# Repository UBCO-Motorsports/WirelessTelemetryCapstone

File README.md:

# WirelessTelemetryCapstone

Please see the UBCO Motorsports wiki page for a full description:
https://sites.google.com/view/ubcomotorsportswiki/electronics/wireless-telemetry-capstone

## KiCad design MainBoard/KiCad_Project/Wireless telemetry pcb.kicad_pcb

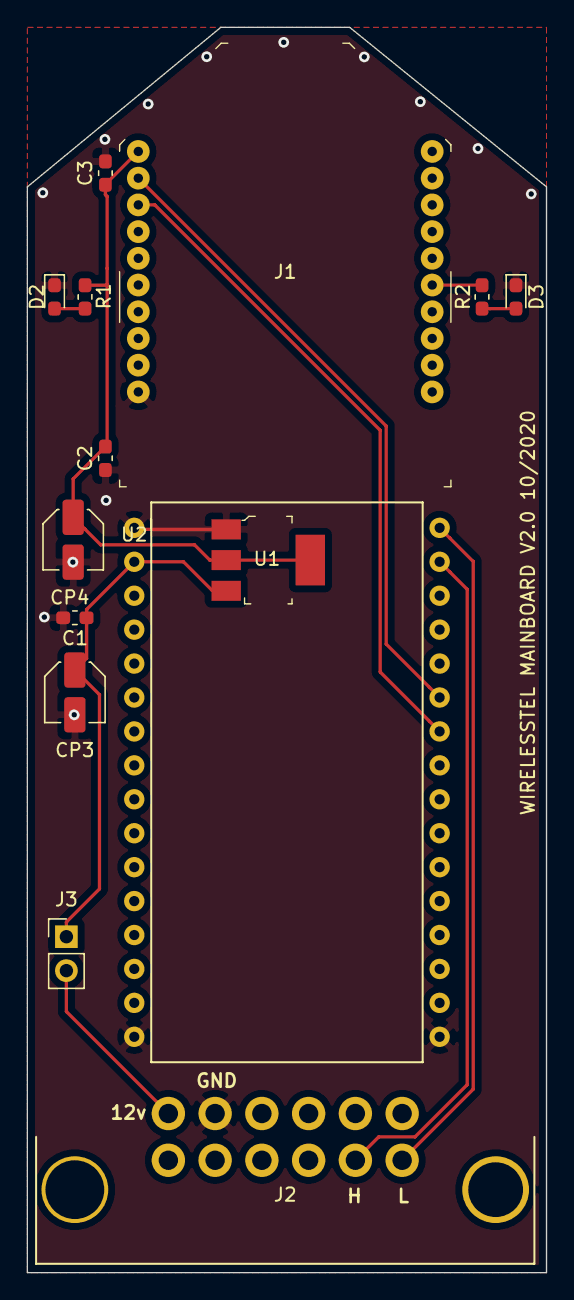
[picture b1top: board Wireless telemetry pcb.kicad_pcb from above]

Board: 2 copper layers, 38.9 x 93.2 mm, 14 parts (0 on the bottom side), 11 nets.

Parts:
C1, C2: 10nF; C_0603_1608Metric_Pad1.05x0.95mm_HandSolder
C3: 8.2pF; C_0603_1608Metric_Pad1.05x0.95mm_HandSolder
CP3, CP4: 10uF; C_Elec_4x5.4
D2, D3: LED; LED_0603_1608Metric_Pad1.05x0.95mm_HandSolder
J1: XBEE; XBEE_PRO-20_THT
J2: Molex MX120; MX120G
J3: PWR HDR; PinHeader_1x02_P2.54mm_Vertical
R1, R2: 220; R_0603_1608Metric_Pad1.05x0.95mm_HandSolder
U1: NCV1117ST33; SOT-223
U2: ControllerBoardV2; ControlBoardV2.0

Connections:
+12V: C1.1, CP3.1, J3.1, U1.3, U2.2
ASSOC: J1.15, R2.2
CANH: J2.11, U2.18
CANL: J2.12, U2.17
GND: C1.2, C2.2, C3.2, CP3.2, CP4.2, D2.1, D3.1, J1.10, J2.2, U1.1, U2.1, U2.16, U2.32
IN: J1.3, U2.23
unnamed: D2.2, R1.1
unnamed: D3.2, R2.1
unnamed: J2.1, J3.2
OUT: J1.2, U2.22
Vcc3.3V: C2.1, C3.1, CP4.1, J1.1, R1.2, U1.2

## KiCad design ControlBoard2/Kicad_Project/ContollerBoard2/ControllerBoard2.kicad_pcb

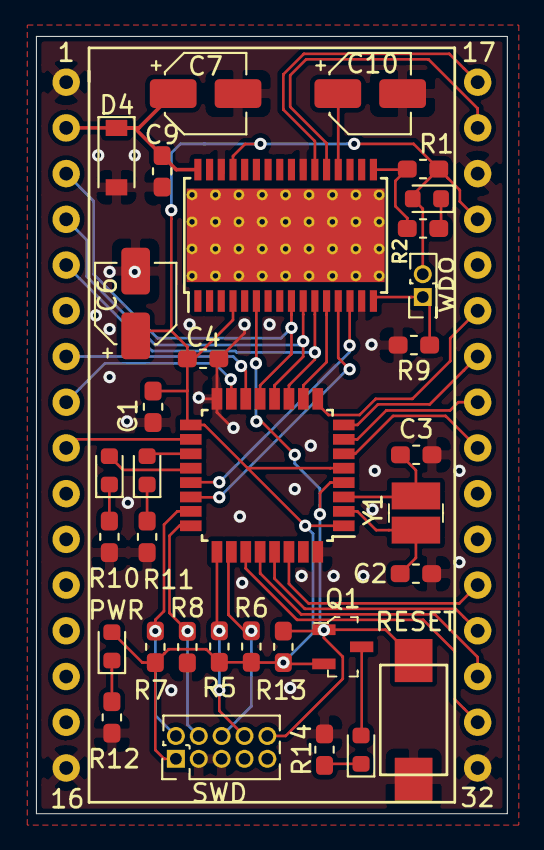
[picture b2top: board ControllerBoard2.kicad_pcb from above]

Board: 2 copper layers, 26.2 x 43.2 mm, 34 parts (0 on the bottom side), 40 nets.

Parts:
C1, C4, C9: 100n; C_0603_1608Metric_Pad1.05x0.95mm_HandSolder
C2, C3: 8p; C_0603_1608Metric_Pad1.05x0.95mm_HandSolder
C6, C7, C10: 10u; CP_Elec_4x5.4
D1, D6: LEDR; LED_0603_1608Metric
D2, D3, D5: LEDG; LED_0603_1608Metric
D4: 30v; D_SOD-123
J1: Main Header; Breadboard_Center_32pin
J2: SWD; PinHeader_2x05_P1.27mm_Vertical
J3: WD_Disable; PinHeader_2x01_P1.27mm_Vertical
Q1: BSS84; SOT-23-3
R1, R5, R6, R7, R8, R13: 10k; R_0603_1608Metric_Pad1.05x0.95mm_HandSolder
R2, R10, R11, R12, R14: 220; R_0603_1608Metric_Pad1.05x0.95mm_HandSolder
R9: 1.3k; R_0603_1608Metric_Pad1.05x0.95mm_HandSolder
S1: RESET; PTS636 SK25F SMTR LFS
U1: STM32F303K8Tx; LQFP-32_7x7mm_P0.8mm
U2: UJA1075A-3.3; HTSSOP-32-1EP_6.1x11mm_P0.65mm_EP5.2x11mm_Mask4.11x4.36mm_T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
Y1: 8Mhz; SMD-2_3.2x2.5mm

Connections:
+3V3: C1.2, C4.1, C6.1, D1.2, D5.2, J1.20, J2.1, J3.2, Q1.2, R1.1, R5.1, R6.1, R7.1, R13.1, U1.1, U1.5, U1.17, U2.4, U2.29
+12V: C7.1, C9.2, D4.1, J1.2, U2.32
CANH: J1.18, U2.21
CANL: J1.17, U2.22
CAN_RX: U1.21, U2.14
CAN_TX: U1.22, U2.13
GND: C1.1, C2.2, C3.2, C4.2, C6.2, C7.2, C9.1, C10.2, D4.2, J1.1, J1.16, J1.19, J1.32, J2.3, J2.5, R8.2, R9.2, R10.1, R11.1, R12.1, R14.2, S1.2, U1.16, U1.32, U2.15, U2.23, U2.30
LIMP: R1.2, R2.2, U2.17
MISO: J1.4, U1.12, U2.10
MOSI: J1.3, U1.13, U2.9
unnamed: C10.1, U2.20
unnamed: D1.1, R2.1
unnamed: D2.1, R10.2
unnamed: D3.1, R11.2
unnamed: D5.1, R12.2
unnamed: D6.1, R14.1
unnamed: D6.2, Q1.3
OSC_IN: C2.1, U1.2, Y1.1
OSC_OUT: C3.1, U1.3, Y1.2
PA0: J1.25, U1.6
PA1: J1.24, U1.7
PA2: J1.23, U1.8
PA3: J1.22, U1.9
PA8: J1.9, U1.18
PA9: D3.2, U1.19
PA10: D2.2, U1.20
PB0: J1.7, U1.14
PB1: J1.8, U1.15
PB4: J1.31, U1.27
PB5: J1.30, U1.28
PB6: J1.29, U1.29
PB7: J1.28, U1.30
RESET: J2.10, Q1.1, R13.2, S1.1, U1.4, U2.6
SCK: J1.5, U1.11, U2.11
SCSN: U1.10, U2.12
SWDCLK: J2.4, R8.1, U1.24
SWDIO: J2.2, R7.2, U1.23
SWO: J2.6, R6.2, U1.26
TDI: J2.8, R5.2, U1.25
WD_OFF: J3.1, R9.1, U2.16

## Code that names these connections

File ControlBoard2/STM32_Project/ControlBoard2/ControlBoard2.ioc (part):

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Mcu.Name=STM32F303K(6-8)Tx
Mcu.Package=LQFP32
Mcu.UserName=STM32F303K8Tx
PA10.GPIOParameters=GPIO_Label
PA10.GPIO_Label=LD1
PA10.Signal=GPIO_Output
PA11.Mode=CAN_Activate
PA11.Signal=CAN_RX
PA12.Mode=CAN_Activate
PA12.Signal=CAN_TX
PA13.Mode=JTAG_4_pins
PA13.Signal=SYS_JTMS-SWDIO
PA14.Mode=JTAG_4_pins
PA14.Signal=SYS_JTCK-SWCLK
PA15.Mode=JTAG_4_pins
PA15.Signal=SYS_JTDI
PA2.Mode=Asynchronous
PA2.Signal=USART2_TX
PA3.Mode=Asynchronous
PA3.Signal=USART2_RX
PA4.GPIOParameters=GPIO_Label
PA4.GPIO_Label=UJA_CS
PA4.Signal=GPIO_Output
PA5.Mode=Full_Duplex_Master
PA5.Signal=SPI1_SCK
PA6.Mode=Full_Duplex_Master
PA6.Signal=SPI1_MISO
PA7.Mode=Full_Duplex_Master
PA7.Signal=SPI1_MOSI
PA9.GPIOParameters=GPIO_Label
PA9.GPIO_Label=LD2
PA9.Signal=GPIO_Output
PB3.Mode=JTAG_4_pins
PB3.Signal=SYS_JTDO-TRACESWO
PB6.Mode=Asynchronous
PB6.Signal=USART1_TX
PB7.Mode=Asynchronous
PB7.Signal=USART1_RX
PF0\ /\ OSC_IN.Mode=HSE-External-Oscillator
PF0\ /\ OSC_IN.Signal=RCC_OSC_IN
PF1\ /\ OSC_OUT.Mode=HSE-External-Oscillator
PF1\ /\ OSC_OUT.Signal=RCC_OSC_OUT
RCC.HSEPLLFreq_Value=8000000
RCC.HSE_VALUE=8000000
RCC.SYSCLKFreq_VALUE=64000000
RCC.SYSCLKSourceVirtual=RCC_SYSCLKSOURCE_PLLCLK
board=custom

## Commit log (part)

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2020-10-07 Updated .gitignore with *.DS_Store
2020-10-07 Consolidated projects
2020-10-07 Deleted
2020-10-07 default project
2020-10-07 Added new task
2020-10-07 deletion
2020-10-07 UART1 to UART2
    Switched from UART1 to UART2 to avoid partial conflicts with CAN master setting. Generated new base code main.c
2020-10-07 test2
2020-10-07 disabled usart1
2020-10-07 Set up Main for Telemetry Viewer
    This is where we can finally start putting everything for the app
2020-10-07 Added basic polar plot function
2020-10-07 Added gitignore folders for pycharm including venv. Deleted cloud dirs
2020-10-07 Removed VENV for CANSimulator project
2020-10-07 remove and retry
2020-10-07 setup messing around
2020-10-08 Improved routing and generated BOM
2020-10-14 Cleaned up ControlBoard schem. Changed viewer to run time domain graph
2020-10-14 Added MainBoard kicad project and worked on V2
2020-10-19 .py code to read serial port and write into a csv file -Roy
2020-10-21 GUI Prototype
    GUI testing
2020-10-21 Added Icon folder
    Icons for toolbars
2020-10-22 Finished MainBoard
2020-10-24 Fixed via net issue on mainboard
2020-10-25 Loader
2020-10-25 Image
2020-10-26 GUI Tweaks
    Added
    - capability to display up to 4 graphs
    - logo to home page
    - beginning of testing technique
    - blank menu options for later use
2020-11-03 Graphing Infrastructure
    Add capability to display up to 16 graphs and improved graph data structures.
    Code is still a shit show...
2020-11-03 Class for Handling Graphs
    Implemented a class (GraphManager) that can handle all the graph widgets and controls the number of graphs being displayed.
2020-11-12 Rough Graph Formatting Fix
    - 8 graph set up still bugged
    - cleaned up some artifact code
2020-11-12 Fixed 8 Graph Display
    Should solve all graph related formatting (I hope)
2020-11-12 Loading screen implemented. Data control infrastructure.
    - Added loading screen to start up of program
    - Added data selection checklist
    - Improved graph selection button functionality
2020-11-12 RPM Dial Added
    Preliminary RPM dial created. Needle jitters though so need to fix that
2020-11-13 RPM Jitter fix
    Fixed jitter by using different png.
    //TO DO move pointer element to front
2020-11-24 RPM->Qwidget + Speedo
2020-11-25 Speedometer added
    Semifinished Speedo added. The needle is bouncy for some reason so I'll fix that later
2020-11-25 PyQT5 and Refactoring
    Created folders for RPM and Speedo images, folder for ui files and fixed library issue
2020-11-25 Speedo Text Fix
    Fixed the text to white so it updates visibly with speed
2020-11-25 Developed procedural generation of CAN filters from message config array
2020-11-25 Split msg config into RAM and the default config into flash
    Default message configuration is memcpy'd into ram at start. The ram message config can then be modified during runtime and CAN filters re-processed.
2020-11-25 Dials added to layout and small formatting
    No functionality in dials yet and lots of display bugs
2020-11-26 CAN config can now be modified over serial, data output completed
2020-11-26 Moved tx buffer to RAM
2020-11-27 Added register definitions for the SBC. Removed offset from CAN config
2020-11-27 Made default value -1 to differ from 0
2020-11-29 Configured SPI to work with SBC. Tuned CAN settings. Added tx frame.
2020-11-29 CAN now functioning properly. Began setup on SBC WDG
2020-11-30 Added CAN output frame and defines for bits. Renamed rx&tx buffers
2020-12-02 Moved stack and heap into CCM ram
2021-01-13 Created Styled Front End
    Added Rudimentary File Browsing
2021-01-14 Context Submenus set for RPM and Speedo
2021-01-14 config menu changes
2021-01-15 Update MainWindow.py
    Menu changes with combobox
2021-01-15 Subclassed PlotWidget
    Created a subclass of pyqtgraph PlotWidget which allows right click context menu to be customized
2021-01-15 Graphing in New GUI and Re-implemented Loading Screen
    -Graphing data in new GUI
    -Added loading screen to new GUI
    -Decreased maximum visible graphs to 12
    -Update() function created for refreshing data
    -Framework for data selection implemented
    -showGraphs() needs a rewrite
2021-01-18 Uploading Serial Code
2021-01-18 Page Selection Button Group
    Adjusted style sheet for page selection buttons and implemented them as a button group for better control
2021-01-18 Serial update
2021-01-19 Cool
2021-01-19 Serial Graphing Test
2021-01-19 Working :)
2021-01-19 Working
2021-01-19 RPM Widget Scaling
2021-01-20 Refresh hide and more
2021-01-20 Refresh and connect setup
2021-01-20 Some minor comments
2021-01-20 Some minor comments 2...
2021-01-20 Moved Port buttons to setup
    Reconstituted names of important things
2021-01-21 Hooked up edit data menu option
    Connected the 'edit data' right click option to show the configuration menu and make changes to the clicked graph
2021-01-21 Connor Update
2021-01-21 Revert "Connor Update"
    This reverts commit fa3433a14c2e76b366baca569b7ee92b35315326.
2021-01-21 Fixed graph combobox
2021-01-21 Available COM Ports TODO
    Added location for the function which will find available COM ports
2021-01-21 Added SerialPort Checking
2021-01-21 COM Port Selection Upgrade
2021-01-21 Get COM ports and return list (working)
2021-01-21 Fixing Git
2021-01-22 Json setup
2021-01-22 pySerial update IMPORTANT
2021-01-22 Serial.py TODO Comment Update
2021-01-22 Highlighting and Bug Improvments
2021-01-22 Remove refresh button and set better colors
2021-01-22 Tiva Testing code
2021-01-22 Log Color to another json
    -fixed issue when hitting cancel when importing CAN file
    -Logging Names and color to new json file for eventual graph use
2021-01-22 sent up send button and grab text
2021-01-23 Subclass of Serial for better control
2021-01-23 Tiva Board Code (Energia) updated and working for testing
2021-01-25 Changes to Tiva board testing code (works) and Just confirmed that the Serial write works for my tests
2021-01-25 remove items from json
    -removes items from json list when clicked on qlistwidget
    -removes items from list and json when importing new CAN list
2021-01-25 Edit Data function hooked up for testing
2021-01-25 Command page completion
    added refresh button back
2021-01-25 preliminary setup for adding radio buttons to config menu
2021-01-26 Added more to json list
2021-01-26 Haltech Json Update
2021-01-27 Progress on watch dog setup over SPI
2021-01-27 CANBUS 2 Update
    updated setup table to include position and size from json
2021-01-27 Telemetry and controllerboard update
2021-01-28 Radio Buttons in config menu
    early implement of it
    - will not refresh if more selected on
    setup page
    itemslogged Json is functioning perfect now
2021-01-28 Regenerated car data array with more channels. Started working on code
2021-01-28 Thing update
2021-01-28 Fixed Part 2
2021-01-28 Highlights graph being edited and scrolling data selection fixed
2021-01-28 Added Return to all send functions
2021-01-28 Apply button set disable color
2021-01-28 fix so the radiobuttons show up again
2021-01-29 Setup all outgoing message ID's to match car for canstim
2021-01-29 Auto-range functionality and graph highlighting
2021-01-30 Graph labeling and highlighting improved
    -Stores the axis labels and titles of the graphs and populates the config menu with them when a graph is selected
2021-01-30 Refactored MainWindow init
2021-01-30 Fixed command page init and config menu init
2021-01-31 'Disable' style sheet for y-range line edit
2021-01-31 CANSTIM now works sending 10 data values to CAN bus from AIM data.
2021-02-01 Fixed scaling of values. Added vehicle shutdown message
2021-02-01 Added colour icons to menus
    Configuration menu and set up page now include colour icons
2021-02-01 Basic keyboard shortcuts
    'i' - import CAN file
    'h' - hide config menu
    'Enter' - applies selected channels in setup page
2021-02-01 Small changes for making filters work.
2021-02-01 Fixed data size graph bug
2021-02-01 Config and apply messages
    -made the config menu look a little nicer
    -fixed error in comboboxs for other graph types
    -made it so if there are less than 16 can messages it sends "0"s in its place
2021-02-01 fixed json index error on import
2021-02-01 thing
2021-02-01 Added delay between sending filter messages to fix bad lukas code
2021-02-02 Threading apply button for slow sending
2021-02-02 Threading for send function working
    only runs once per call and app stays fully responsive during the send/sleeps
2021-02-02 Small change to icon generation code and spacing of functions
2021-02-03 Populate y-range data when configuration menu is called
2021-02-03 Re-enabled serial for filter upload
2021-02-04 Fixed serial logic
2021-02-05 RPM and Speedo Scaling
2021-02-07 Random junk from testing
2021-02-07 Dial Visual Glitch fix
2021-02-08 Rename of tiveboard testing files to make more sense.
2021-02-09 Watchdog WORKS!!!!!!!!!!!!!!!!!!!!!!!!!!!!!!!!!!!!!!!!!!!!!!!!!!!!!!!!!!
2021-02-10 Scaling & Offset done, 16 data Arrays created!
2021-02-11 Serial fix
2021-02-11 RPM and speedo int fix with scaling
2021-02-11 Rough way to get multiple speedos working
2021-02-11 import and save default list items in setup
2021-02-13 Polar plot subclass and Serial Refactor
2021-02-13 Polar Plot config menu
2021-02-13 Data selection prototype and fully functioning time graphing/speedo
2021-02-13 Polar plot ranging, plotting and config functionality
2021-02-13 Dropped minutes and secs from samples config
2021-02-14 Saving and Importing Button functionality started
2021-02-14 Time Stamps!
    Also fixed polar plot auto range bug
2021-02-14 Removing old TODO
2021-02-16 Selected speedo highlighting
2021-02-16 Fixed timezone error for timestamps
2021-02-16 Widget highlighting fixed when config hide is called
2021-02-17 Fixed random serial jumps somehow and fixed filter sending
    *starts twerking*
2021-02-17 Sending filters after micro restarts now works
2021-02-17 Fixed shortcuts and removed old code from GraphManager
2021-02-17 shortcuts added to label on home screen
    uwu
2021-02-17 Remove legend
2021-02-17 Import functionality for time domain graphs
2021-02-19 Save/load graph page layout and config menu population when called
2021-02-19 Fixed update bug for gauges
2021-02-19 Actually fixed update bug for gauges
2021-02-20 Fixed polar plot autoranging and samples
    Fixed time domain config menu calling
2021-02-22 Setup page ease of use
2021-02-25 Fixed list highlighting for default load and finished set up page
2021-02-25 Reenabled loader/Cleaned up print statements and old commented code
    -Set minimum size of main window
2021-02-25 Potential freeze fix
2021-02-27 Added window icon, window title and taskbar icon
2021-03-11 Additional shutdown button
2021-03-11 Cleaned up code and added comments
2021-03-15 Random clean up and exe
2021-03-16 Git Fix
2021-03-16 Latest exe
2021-10-15 Refactored ControlBoard source code
    Split functionality into separate files. Hardware-abstracted all files using hardware handle structs. Brought UJA1075 functionality into own driver. Fixed command comparison of casted chars into defi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
2021-10-15 More ControlBoard improvements. Converted rest of structs to typedefs. Reorganized folder structure. Seperated UJA transfer into own function. Created a few more defines for magic numbers.
2021-10-16 Few more small improvements
    Rearranging of constants. Fixed ISR instance comparisons and added for CAN ISR. Added nullptr checks to ControlBoard init in the form of asserts.
2021-10-16 Changed magic number 16 to a define, CAN_TOTAL_FILTERS
2021-10-21 Updated readme to include wiki page link
2022-03-27 Fixed ProcessCommandSemaphore_Handle being a pointer instead of an instance.
